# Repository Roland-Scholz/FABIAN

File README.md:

# Fa Bi An
FAbulous BInary ANihilator

A simple Z80 based CP/M system. You'll find here:

- KiCad files for the pcb
- 6-chip Z80 hardware
- 64KB static RAM
- 8/16/32KB (EP)ROM, here a 2764A version is used (8KB, 12,5V pgm voltage)
- 68681 double UART operating at 115200 baud
- one serial line connects to a VT100 terminal, the 2nd one to the CP/M disk server (two TTL to RS232 converters needed)
- GAL 16V8 providing glue logic (fabian.pld, connect PIN 5 and 15 with a pice of wire)
- WinCUPL https://www.microchip.com/en-us/products/fpgas-and-plds/spld-cplds/pld-design-resources)
- CP/M-2.2 and simple BIOS source code (CP/M at $E400, BIOS at $FA00)
- Windows based build files
- Serial CP/M disk server written in Java
- 8 output pins (7 usable, OP7 toggels ROM on/off)
- 6 input pins
- I have some PCBs left, write to rolandscholz@gmx.de if you want one

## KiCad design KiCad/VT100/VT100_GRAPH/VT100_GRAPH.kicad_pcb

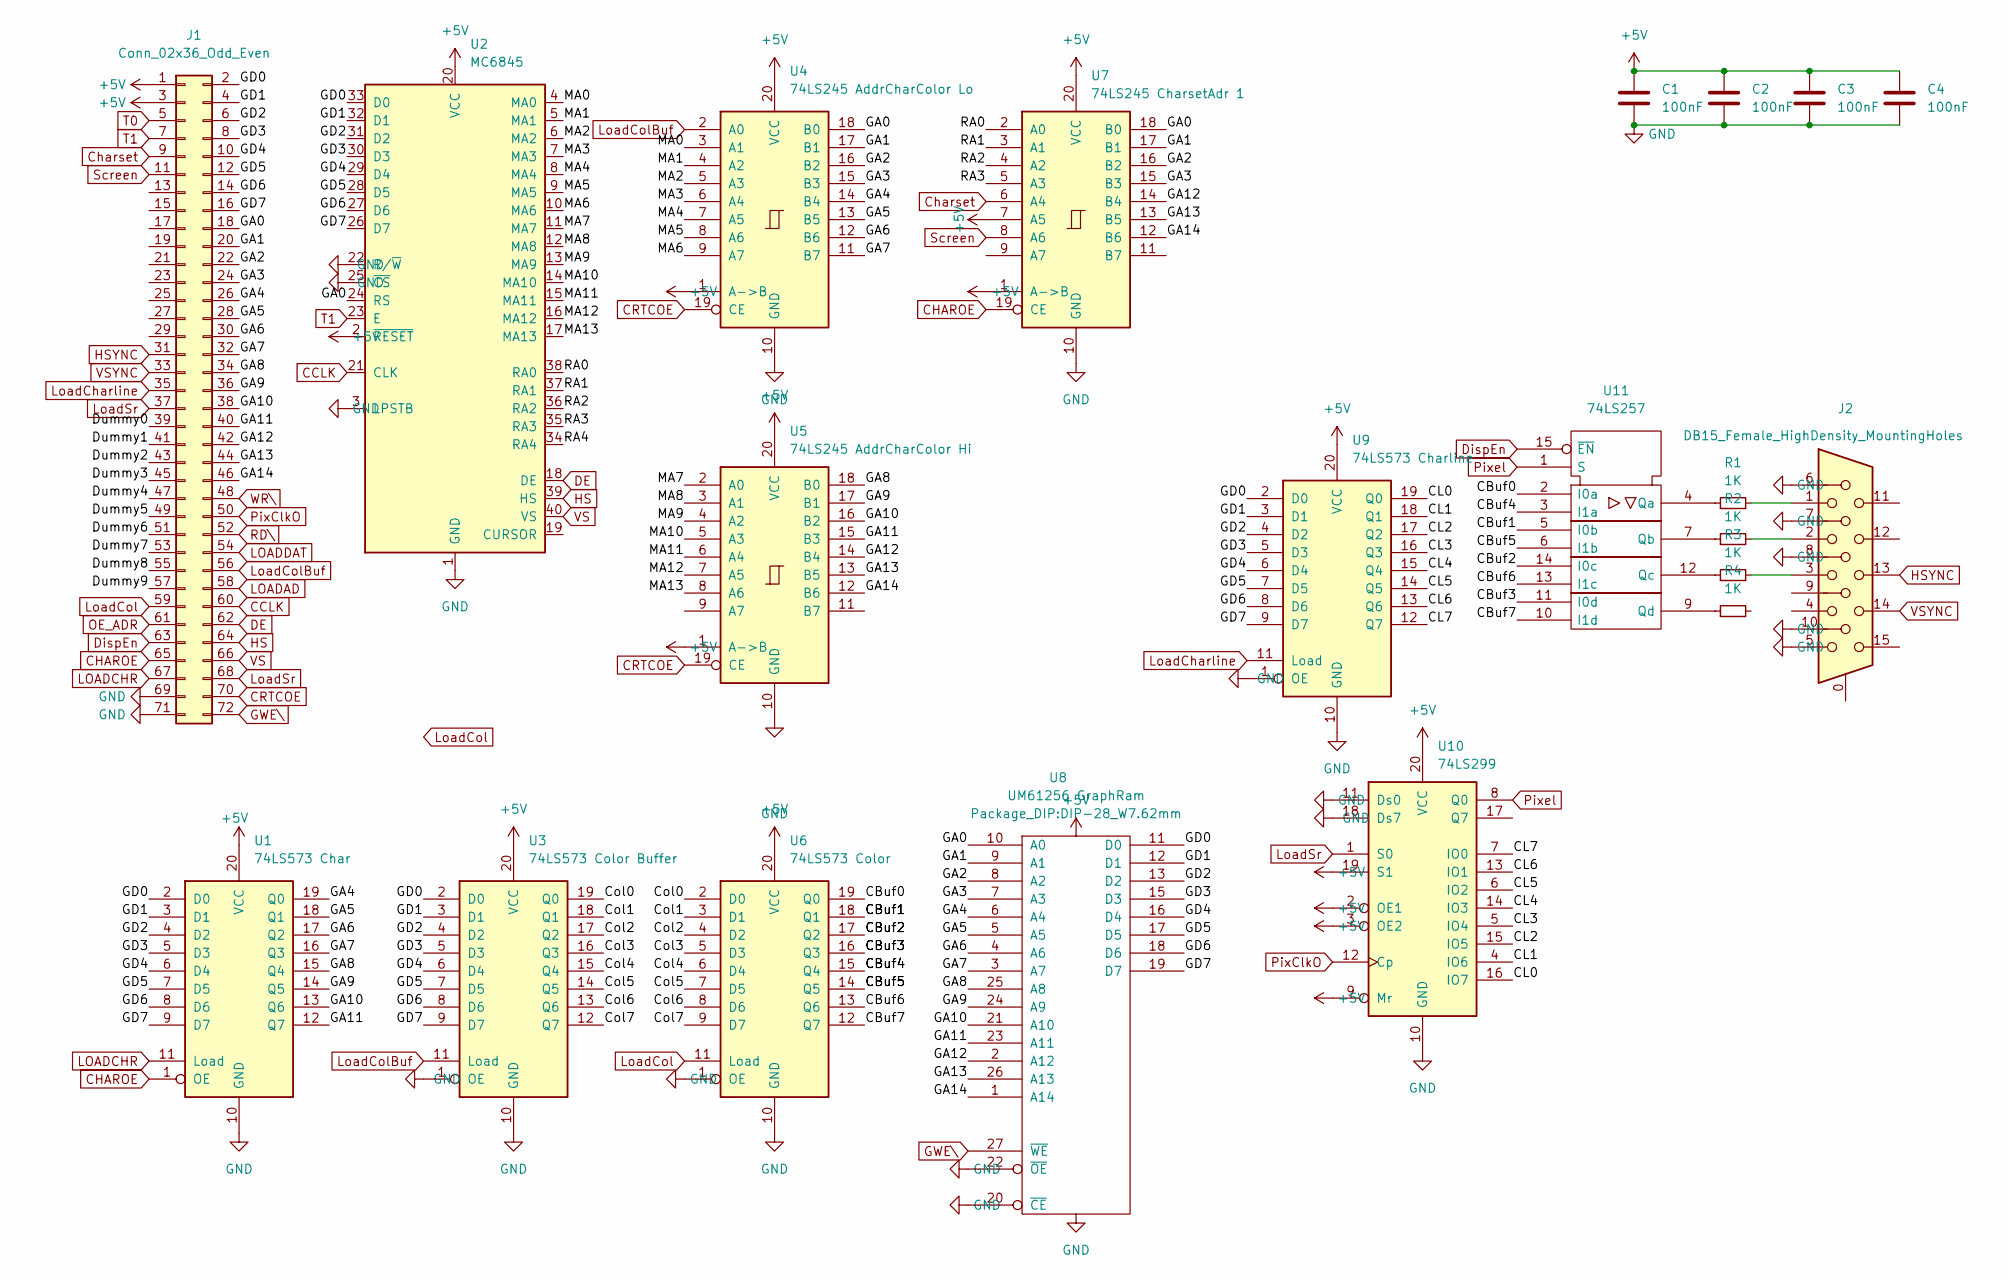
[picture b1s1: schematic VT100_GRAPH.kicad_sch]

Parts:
C1, C2, C3, C4: 100nF; C_Rect_L7.0mm_W2.0mm_P5.00mm
J1: Conn_02x36_Odd_Even; PinSocket_2x36_P2.54mm_Vertical
J2: DB15_Female_HighDensity_MountingHoles; DSUB-15-HD_Female_Horizontal_P2.29x1.98mm_EdgePinOffset3.03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
R1, R2, R3, R4: 1K; R_Axial_DIN0204_L3.6mm_D1.6mm_P1.90mm_Vertical
U1: 74LS573 Char; DIP-20_W7.62mm
U2: MC6845; DIP-40_W15.24mm
U3: 74LS573 Color Buffer; DIP-20_W7.62mm
U4: 74LS245 AddrCharColor Lo; DIP-20_W7.62mm
U5: 74LS245 AddrCharColor Hi; DIP-20_W7.62mm
U6: 74LS573 Color; DIP-20_W7.62mm
U7: 74LS245 CharsetAdr 1; DIP-20_W7.62mm
U8: UM61256 GraphRam; DIP-28_W7.62mm
U9: 74LS573 Charline; DIP-20_W7.62mm
U10: 74LS299; DIP-20_W7.62mm
U11: 74LS257; DIP-16_W7.62mm

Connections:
+5V: C1.1, C2.1, C3.1, C4.1, J1.1, J1.3, U1.20 (VCC), U2.2 (~RESET), U2.20 (VCC), U3.20 (VCC), U4.1 (A->B), U4.20 (VCC), U5.1 (A->B), U5.20 (VCC), U6.20 (VCC), U7.1 (A->B), U7.7 (A5), U7.20 (VCC), U8.28 (VCC), U9.20 (VCC), U10.2 (OE1), U10.3 (OE2), U10.9 (Mr), U10.19 (S1), U10.20 (VCC), U11.16 (VCC)
/CBuf0: U6.19 (Q0), U11.2 (I0a)
/CBuf1: U6.18 (Q1), U11.5 (I0b)
/CBuf2: U6.17 (Q2), U11.14 (I0c)
/CBuf3: U6.16 (Q3), U11.11 (I0d)
/CBuf4: U6.15 (Q4), U11.3 (I1a)
/CBuf5: U6.14 (Q5), U11.6 (I1b)
/CBuf6: U6.13 (Q6), U11.13 (I1c)
/CBuf7: U6.12 (Q7), U11.10 (I1d)
/CL0: U9.19 (Q0), U10.16 (IO7)
/CL1: U9.18 (Q1), U10.4 (IO6)
/CL2: U9.17 (Q2), U10.15 (IO5)
/CL3: U9.16 (Q3), U10.5 (IO4)
/CL4: U9.15 (Q4), U10.14 (IO3)
/CL5: U9.14 (Q5), U10.6 (IO2)
/CL6: U9.13 (Q6), U10.13 (IO1)
/CL7: U9.12 (Q7), U10.7 (IO0)
/Col0: U3.19 (Q0), U6.2 (D0)
/Col1: U3.18 (Q1), U6.3 (D1)
/Col2: U3.17 (Q2), U6.4 (D2)
/Col3: U3.16 (Q3), U6.5 (D3)
/Col4: U3.15 (Q4), U6.6 (D4)
/Col5: U3.14 (Q5), U6.7 (D5)
/Col6: U3.13 (Q6), U6.8 (D6)
/Col7: U3.12 (Q7), U6.9 (D7)
/Dummy0: J1.39
/Dummy1: J1.41
/Dummy2: J1.43
/Dummy3: J1.45
/Dummy4: J1.47
/Dummy5: J1.49
/Dummy6: J1.51
/Dummy7: J1.53
/Dummy8: J1.55
/Dummy9: J1.57
/GA0: J1.18, U2.24 (RS), U4.18 (B0), U7.18 (B0), U8.10 (A0)
/GA1: J1.20, U4.17 (B1), U7.17 (B1), U8.9 (A1)
/GA2: J1.22, U4.16 (B2), U7.16 (B2), U8.8 (A2)
/GA3: J1.24, U4.15 (B3), U7.15 (B3), U8.7 (A3)
/GA4: J1.26, U1.19 (Q0), U4.14 (B4), U8.6 (A4)
/GA5: J1.28, U1.18 (Q1), U4.13 (B5), U8.5 (A5)
/GA6: J1.30, U1.17 (Q2), U4.12 (B6), U8.4 (A6)
/GA7: J1.32, U1.16 (Q3), U4.11 (B7), U8.3 (A7)
/GA8: J1.34, U1.15 (Q4), U5.18 (B0), U8.25 (A8)
/GA9: J1.36, U1.14 (Q5), U5.17 (B1), U8.24 (A9)
/GA10: J1.38, U1.13 (Q6), U5.16 (B2), U8.21 (A10)
/GA11: J1.40, U1.12 (Q7), U5.15 (B3), U8.23 (A11)
/GA12: J1.42, U5.14 (B4), U7.14 (B4), U8.2 (A12)
/GA13: J1.44, U5.13 (B5), U7.13 (B5), U8.26 (A13)
/GA14: J1.46, U5.12 (B6), U7.12 (B6), U8.1 (A14)
/GD0: J1.2, U1.2 (D0), U2.33 (D0), U3.2 (D0), U8.11 (D0), U9.2 (D0)
/GD1: J1.4, U1.3 (D1), U2.32 (D1), U3.3 (D1), U8.12 (D1), U9.3 (D1)
/GD2: J1.6, U1.4 (D2), U2.31 (D2), U3.4 (D2), U8.13 (D2), U9.4 (D2)
/GD3: J1.8, U1.5 (D3), U2.30 (D3), U3.5 (D3), U8.15 (D3), U9.5 (D3)
/GD4: J1.10, U1.6 (D4), U2.29 (D4), U3.6 (D4), U8.16 (D4), U9.6 (D4)
/GD5: J1.12, U1.7 (D5), U2.28 (D5), U3.7 (D5), U8.17 (D5), U9.7 (D5)
/GD6: J1.14, U1.8 (D6), U2.27 (D6), U3.8 (D6), U8.18 (D6), U9.8 (D6)
/GD7: J1.16, U1.9 (D7), U2.26 (D7), U3.9 (D7), U8.19 (D7), U9.9 (D7)
/MA0: U2.4 (MA0), U4.3 (A1)
/MA1: U2.5 (MA1), U4.4 (A2)
/MA2: U2.6 (MA2), U4.5 (A3)
/MA3: U2.7 (MA3), U4.6 (A4)
/MA4: U2.8 (MA4), U4.7 (A5)
/MA5: U2.9 (MA5), U4.8 (A6)
/MA6: U2.10 (MA6), U4.9 (A7)
/MA7: U2.11 (MA7), U5.2 (A0)
/MA8: U2.12 (MA8), U5.3 (A1)
/MA9: U2.13 (MA9), U5.4 (A2)
/MA10: U2.14 (MA10), U5.5 (A3)
/MA11: U2.15 (MA11), U5.6 (A4)
/MA12: U2.16 (MA12), U5.7 (A5)
/MA13: U2.17 (MA13), U5.8 (A6)
/RA0: U2.38 (RA0), U7.2 (A0)
/RA1: U2.37 (RA1), U7.3 (A1)
/RA2: U2.36 (RA2), U7.4 (A2)
/RA3: U2.35 (RA3), U7.5 (A3)
/RA4: U2.34 (RA4)
CCLK: J1.60, U2.21 (CLK)
CHAROE: J1.65, U1.1 (OE), U7.19 (CE)
CRTCOE: J1.70, U4.19 (CE), U5.19 (CE)
Charset: J1.9, U7.6 (A4)
DE: J1.62, U2.18 (DE)
DispEn: J1.63, U11.15 (~EN)
GND: C1.2, C2.2, C3.2, C4.2, J1.69, J1.71, J2.5, J2.6, J2.7, J2.8, J2.10, U1.10 (GND), U2.1 (GND), U2.3 (LPSTB), U2.22 (R/~W), U2.25 (~CS), U3.1 (OE), U3.10 (GND), U4.10 (GND), U5.10 (GND), U6.1 (OE), U6.10 (GND), U7.10 (GND), U8.14 (GND), U8.20 (~CE), U8.22 (~OE), U9.1 (OE), U9.10 (GND), U10.10 (GND), U10.11 (Ds0), U10.18 (Ds7), U11.8 (GND)
GWE\: J1.72, U8.27 (~WE)
HS: J1.64, U2.39 (HS)
HSYNC: J1.31, J2.13
LOADAD: J1.58
LOADCHR: J1.67, U1.11 (Load)
LOADDAT: J1.54
LoadCharline: J1.35, U9.11 (Load)
LoadCol: J1.59, U6.11 (Load)
LoadColBuf: J1.56, U3.11 (Load), U4.2 (A0)
LoadSr: J1.37, J1.68, U10.1 (S0)
unnamed: J2.1, R1.2
unnamed: J2.2, R2.2
unnamed: J2.3, R3.2
unnamed: R1.1, U11.4 (Qa)
unnamed: R2.1, U11.7 (Qb)
unnamed: R3.1, U11.12 (Qc)
unnamed: R4.1, U11.9 (Qd)
OE_ADR: J1.61
PixClkO: J1.50, U10.12 (Cp)
Pixel: U10.8 (Q0), U11.1 (S)
RD\: J1.52
Screen: J1.11, U7.8 (A6)
T0: J1.5
T1: J1.7, U2.23 (E)
VS: J1.66, U2.40 (VS)
VSYNC: J1.33, J2.14
WR\: J1.48

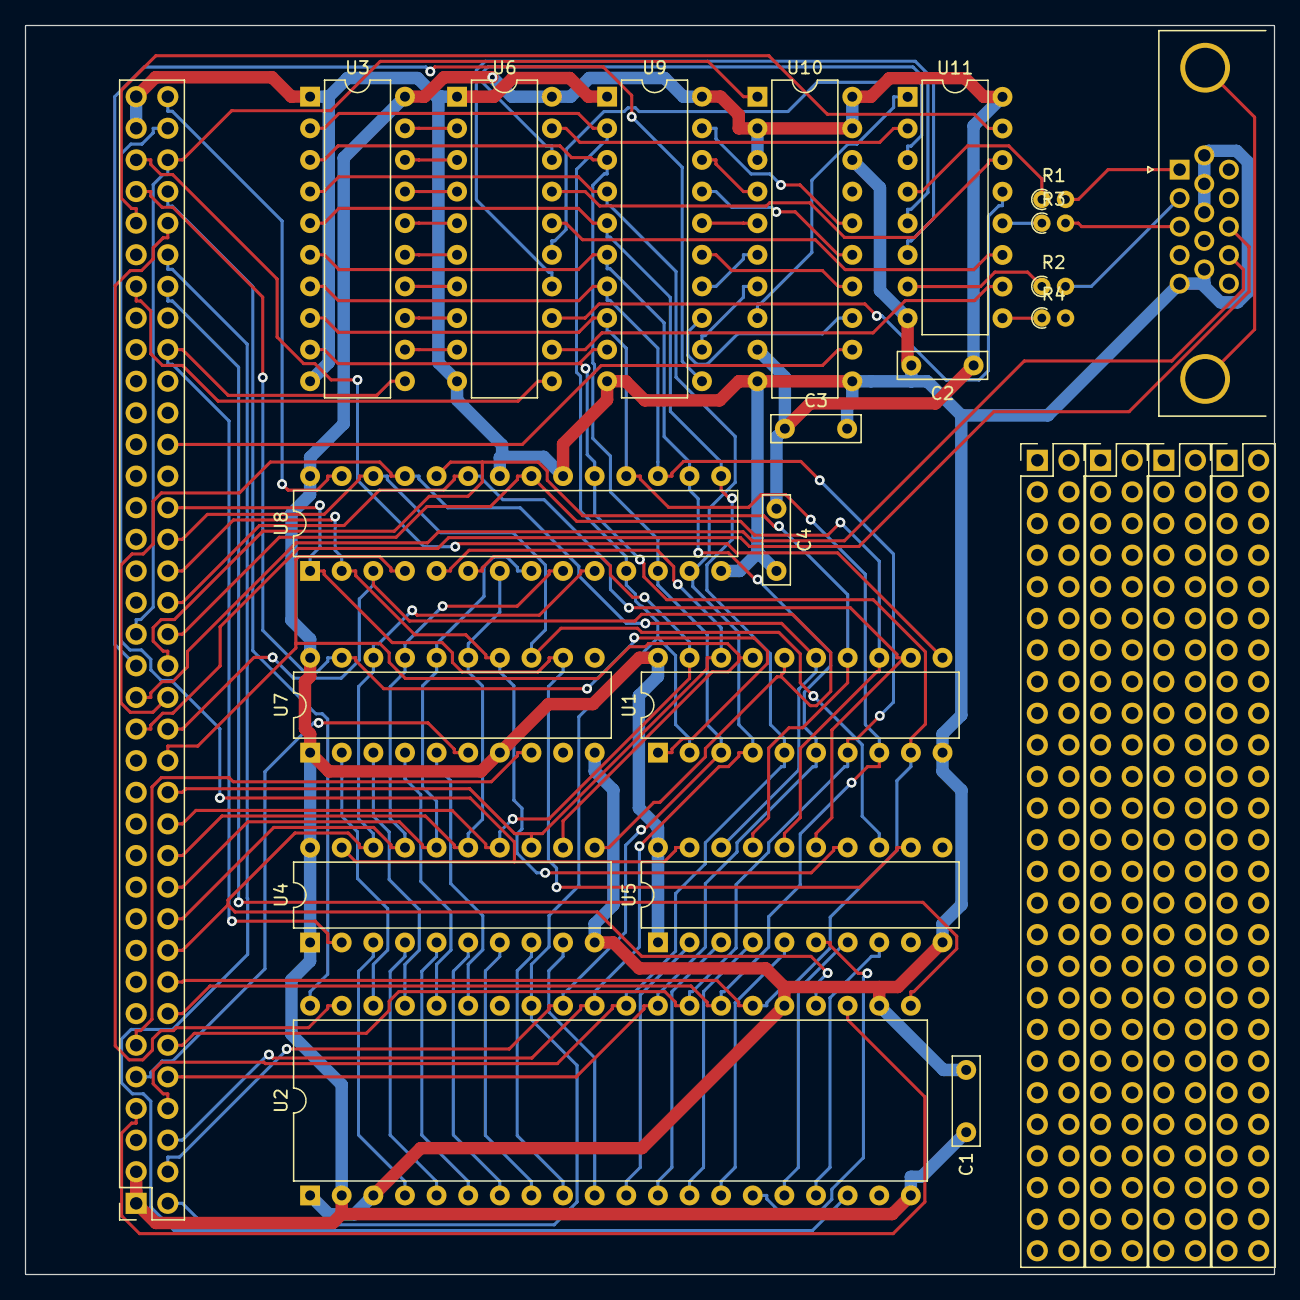
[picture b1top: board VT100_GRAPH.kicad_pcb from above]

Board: 2 copper layers, 100.3 x 100.3 mm, 21 parts (0 on the bottom side), 94 nets.

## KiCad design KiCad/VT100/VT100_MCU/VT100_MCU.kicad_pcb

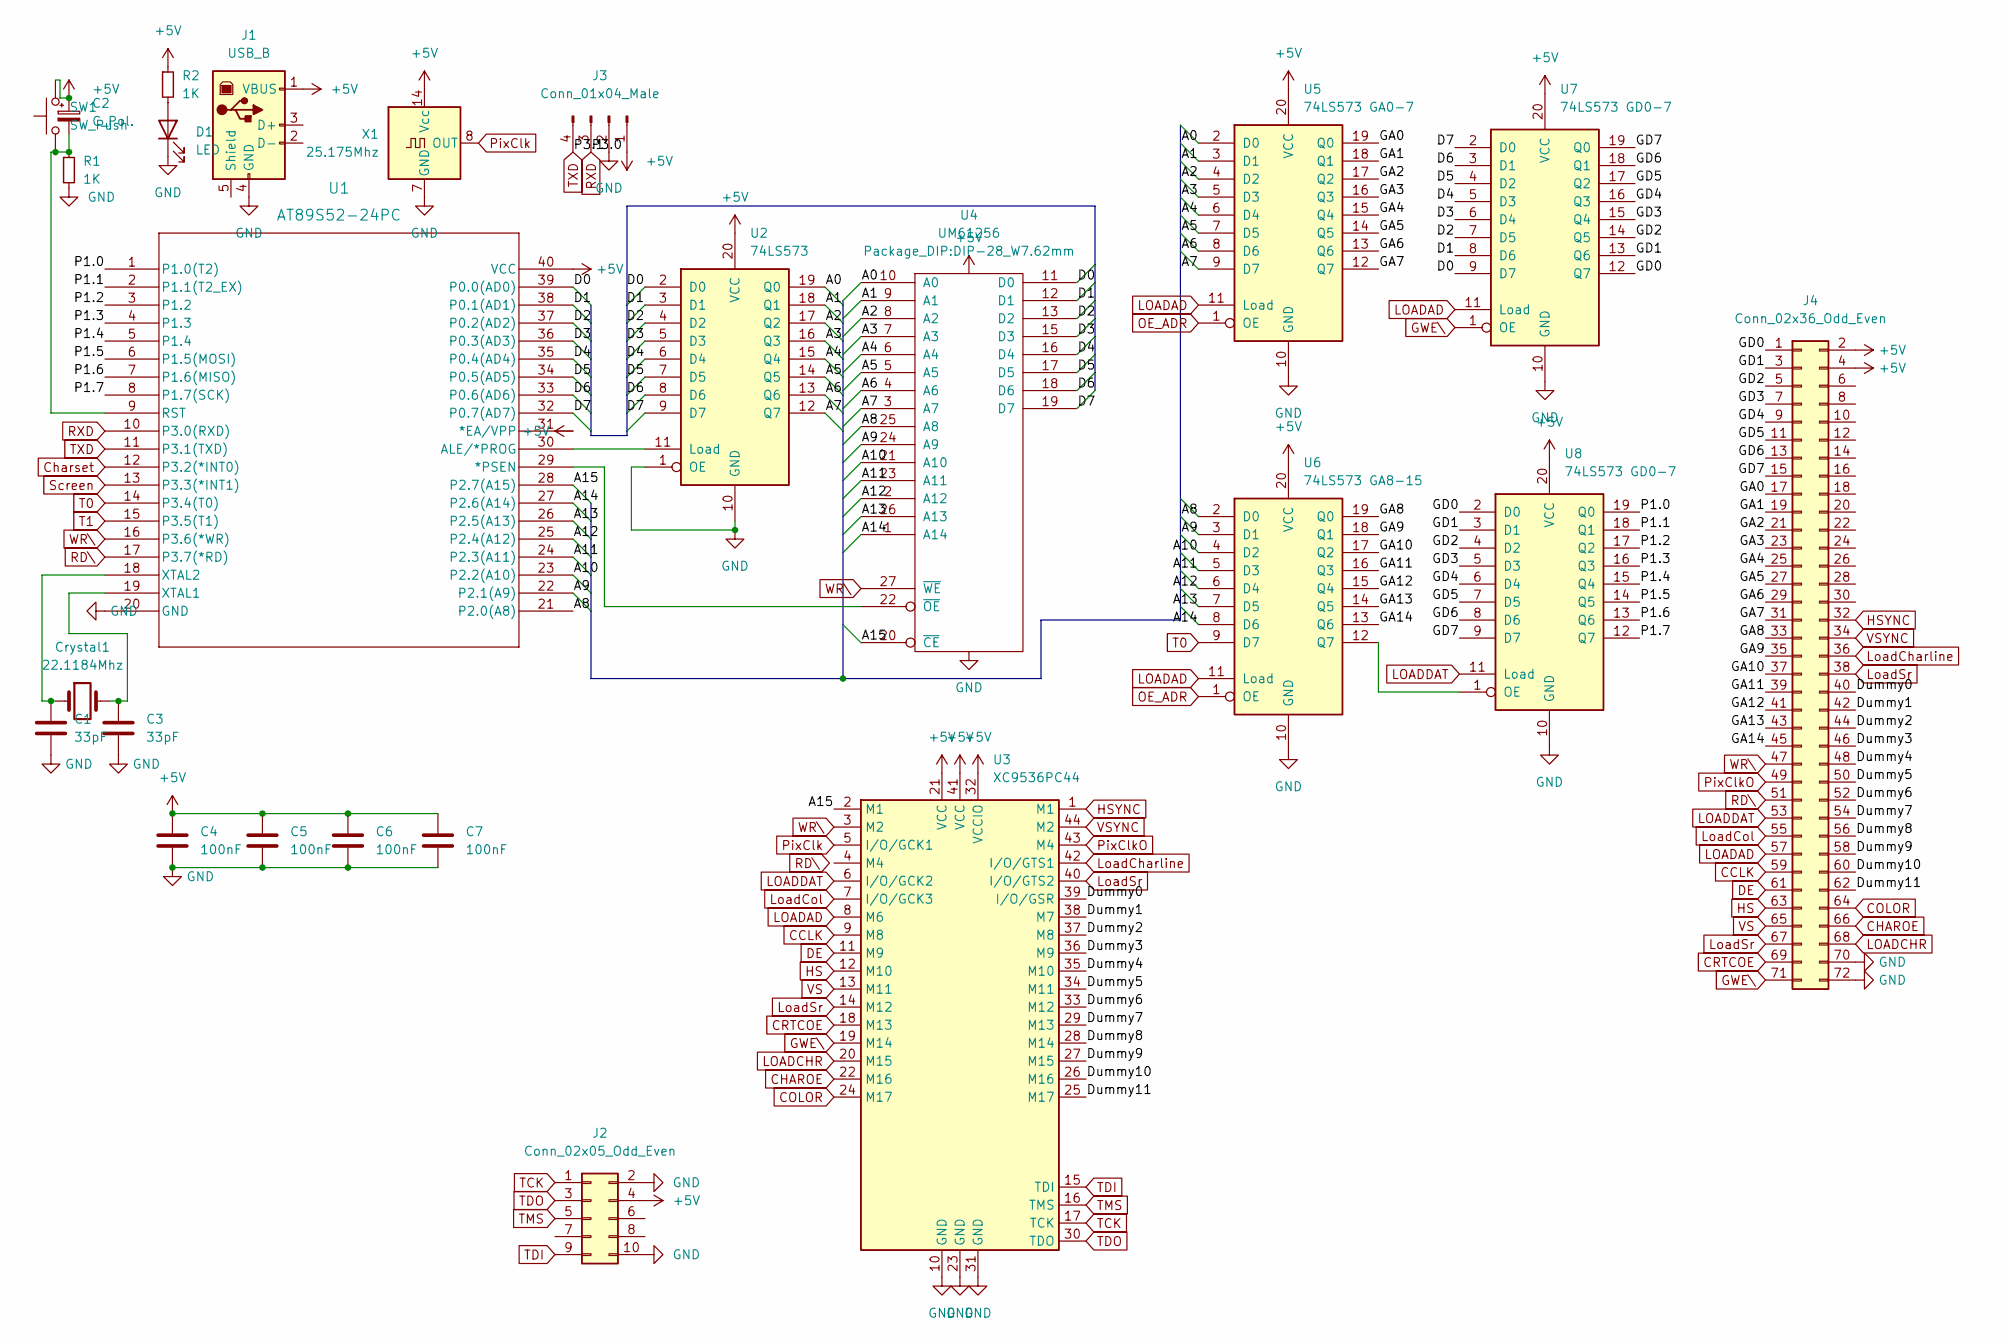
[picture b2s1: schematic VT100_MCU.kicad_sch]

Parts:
C1, C3: 33pF; PinHeader_1x02_P2.54mm_Vertical
C2: C_Pol.; CP_Radial_D5.0mm_P2.50mm
C4, C5, C6, C7: 100nF; PinHeader_1x02_P2.54mm_Vertical
Crystal1: 22.1184Mhz; Crystal_HC18-U_Vertical
D1: LED; LED_D5.0mm
J1: USB_B; USB_B_Lumberg_2411_02_Horizontal
J2: Conn_02x05_Odd_Even; PinHeader_2x05_P2.54mm_Vertical
J3: Conn_01x04_Male; PinHeader_1x04_P2.54mm_Vertical
J4: Conn_02x36_Odd_Even; PinSocket_2x36_P2.54mm_Horizontal
R1, R2: 1K; R_Axial_DIN0204_L3.6mm_D1.6mm_P1.90mm_Vertical
SW1: SW_Push; C_Rect_L7.5mm_W6.5mm_P5.00mm
U1: AT89S52-24PC; DIP-40_W15.24mm
U2: 74LS573; DIP-20_W7.62mm
U3: XC9536PC44; PLCC-44_THT-Socket
U4: UM61256; DIP-28_W7.62mm
U5: 74LS573 GA0-7; DIP-20_W7.62mm
U6: 74LS573 GA8-15; DIP-20_W7.62mm
U7, U8: 74LS573 GD0-7; DIP-20_W7.62mm
X1: 25.175Mhz; Oscillator_DIP-14

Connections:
+5V: C2.1, C4.1, C5.1, C6.1, C7.1, J1.1 (VBUS), J2.4, J3.1, J4.2, J4.4, R2.1, SW1.2, U1.31 (*EA/VPP), U1.40 (VCC), U2.20 (VCC), U3.21 (VCC), U3.32 (VCCIO), U3.41 (VCC), U4.28 (VCC), U5.20 (VCC), U6.20 (VCC), U7.20 (VCC), U8.20 (VCC), X1.14 (Vcc)
/A0: U2.19 (Q0), U4.10 (A0), U5.2 (D0)
/A1: U2.18 (Q1), U4.9 (A1), U5.3 (D1)
/A2: U2.17 (Q2), U4.8 (A2), U5.4 (D2)
/A3: U2.16 (Q3), U4.7 (A3), U5.5 (D3)
/A4: U2.15 (Q4), U4.6 (A4), U5.6 (D4)
/A5: U2.14 (Q5), U4.5 (A5), U5.7 (D5)
/A6: U2.13 (Q6), U4.4 (A6), U5.8 (D6)
/A7: U2.12 (Q7), U4.3 (A7), U5.9 (D7)
/A8: U1.21 (P2.0(A8)), U4.25 (A8), U6.2 (D0)
/A9: U1.22 (P2.1(A9)), U4.24 (A9), U6.3 (D1)
/A10: U1.23 (P2.2(A10)), U4.21 (A10), U6.4 (D2)
/A11: U1.24 (P2.3(A11)), U4.23 (A11), U6.5 (D3)
/A12: U1.25 (P2.4(A12)), U4.2 (A12), U6.6 (D4)
/A13: U1.26 (P2.5(A13)), U4.26 (A13), U6.7 (D5)
/A14: U1.27 (P2.6(A14)), U4.1 (A14), U6.8 (D6)
/A15: U1.28 (P2.7(A15)), U3.2 (M1), U4.20 (~CE)
/D0: U1.39 (P0.0(AD0)), U2.2 (D0), U4.11 (D0), U7.9 (D7)
/D1: U1.38 (P0.1(AD1)), U2.3 (D1), U4.12 (D1), U7.8 (D6)
/D2: U1.37 (P0.2(AD2)), U2.4 (D2), U4.13 (D2), U7.7 (D5)
/D3: U1.36 (P0.3(AD3)), U2.5 (D3), U4.15 (D3), U7.6 (D4)
/D4: U1.35 (P0.4(AD4)), U2.6 (D4), U4.16 (D4), U7.5 (D3)
/D5: U1.34 (P0.5(AD5)), U2.7 (D5), U4.17 (D5), U7.4 (D2)
/D6: U1.33 (P0.6(AD6)), U2.8 (D6), U4.18 (D6), U7.3 (D1)
/D7: U1.32 (P0.7(AD7)), U2.9 (D7), U4.19 (D7), U7.2 (D0)
/Dummy0: J4.40, U3.39 (I/O/GSR)
/Dummy1: J4.42, U3.38 (M7)
/Dummy2: J4.44, U3.37 (M8)
/Dummy3: J4.46, U3.36 (M9)
/Dummy4: J4.48, U3.35 (M10)
/Dummy5: J4.50, U3.34 (M11)
/Dummy6: J4.52, U3.33 (M12)
/Dummy7: J4.54, U3.29 (M13)
/Dummy8: J4.56, U3.28 (M14)
/Dummy9: J4.58, U3.27 (M15)
/Dummy10: J4.60, U3.26 (M16)
/GA0: J4.17, U5.19 (Q0)
/GA1: J4.19, U5.18 (Q1)
/GA2: J4.21, U5.17 (Q2)
/GA3: J4.23, U5.16 (Q3)
/GA4: J4.25, U5.15 (Q4)
/GA5: J4.27, U5.14 (Q5)
/GA6: J4.29, U5.13 (Q6)
/GA7: J4.31, U5.12 (Q7)
/GA8: J4.33, U6.19 (Q0)
/GA9: J4.35, U6.18 (Q1)
/GA10: J4.37, U6.17 (Q2)
/GA11: J4.39, U6.16 (Q3)
/GA12: J4.41, U6.15 (Q4)
/GA13: J4.43, U6.14 (Q5)
/GA14: J4.45, U6.13 (Q6)
/GD0: J4.1, U7.12 (Q7), U8.2 (D0)
/GD1: J4.3, U7.13 (Q6), U8.3 (D1)
/GD2: J4.5, U7.14 (Q5), U8.4 (D2)
/GD3: J4.7, U7.15 (Q4), U8.5 (D3)
/GD4: J4.9, U7.16 (Q3), U8.6 (D4)
/GD5: J4.11, U7.17 (Q2), U8.7 (D5)
/GD6: J4.13, U7.18 (Q1), U8.8 (D6)
/GD7: J4.15, U7.19 (Q0), U8.9 (D7)
/P1.0: U1.1 (P1.0(T2)), U8.19 (Q0)
/P1.1: U1.2 (P1.1(T2_EX)), U8.18 (Q1)
/P1.2: U1.3 (P1.2), U8.17 (Q2)
/P1.3: U1.4 (P1.3), U8.16 (Q3)
/P1.4: U1.5 (P1.4), U8.15 (Q4)
/P1.5: U1.6 (P1.5(MOSI)), U8.14 (Q5)
/P1.6: U1.7 (P1.6(MISO)), U8.13 (Q6)
/P1.7: U1.8 (P1.7(SCK)), U8.12 (Q7)
CCLK: J4.59, U3.9 (M8)
CHAROE: J4.66, U3.22 (M16)
CRTCOE: J4.69, U3.18 (M13)
Charset: J4.10, U1.12 (P3.2(*INT0))
DE: J4.61, U3.11 (M9)
DispEn: J4.64, U3.24 (M17)
GND: C1.2, C3.2, C4.2, C5.2, C6.2, C7.2, D1.1 (K), J1.4 (GND), J2.2, J2.10, J3.2, J4.70, J4.72, R1.2, U1.20 (GND), U2.1 (OE), U2.10 (GND), U3.10 (GND), U3.23 (GND), U3.31 (GND), U4.14 (GND), U5.10 (GND), U6.10 (GND), U7.10 (GND), U8.10 (GND), X1.7 (GND)
GWE\: J4.71, U3.19 (M14), U7.1 (OE)
HS: J4.63, U3.12 (M10)
HSYNC: J4.32, U3.1 (M1)
LOADAD: J4.57, U3.8 (M6), U5.11 (Load), U6.11 (Load), U7.11 (Load)
LOADCHR: J4.68, U3.20 (M15)
LOADDAT: J4.53, U3.6 (I/O/GCK2), U8.11 (Load)
LoadCharline: J4.36, U3.42 (I/O/GTS1)
LoadCol: J4.55, U3.7 (I/O/GCK3)
LoadSr: J4.38, J4.67, U3.14 (M12), U3.40 (I/O/GTS2)
unnamed: C1.1, Crystal1.1, U1.18 (XTAL2)
unnamed: C2.2, R1.1, SW1.1, U1.9 (RST)
unnamed: C3.1, Crystal1.2, U1.19 (XTAL1)
unnamed: D1.2 (A), R2.2
unnamed: U1.29 (*PSEN), U4.22 (~OE)
unnamed: U1.30 (ALE/*PROG), U2.11 (Load)
unnamed: U6.12 (Q7), U8.1 (OE)
PixClk: U3.5 (I/O/GCK1), X1.8 (OUT)
PixClkO: J4.49, U3.43 (M4)
RD\: J4.51, U1.17 (P3.7(*RD)), U3.4 (M4)
RXD: J3.3, U1.10 (P3.0(RXD))
Screen: J4.12, U1.13 (P3.3(*INT1))
T0: J4.6, U1.14 (P3.4(T0)), U6.9 (D7)
T1: J4.8, U1.15 (P3.5(T1))
TCK: J2.1, U3.17 (TCK)
TDI: J2.9, U3.15 (TDI)
TDO: J2.3, U3.30 (TDO)
TMS: J2.5, U3.16 (TMS)
TXD: J3.4, U1.11 (P3.1(TXD))
VS: J4.65, U3.13 (M11)
VSYNC: J4.34, U3.44 (M2)
WR\: J4.47, U1.16 (P3.6(*WR)), U3.3 (M2), U4.27 (~WE)

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
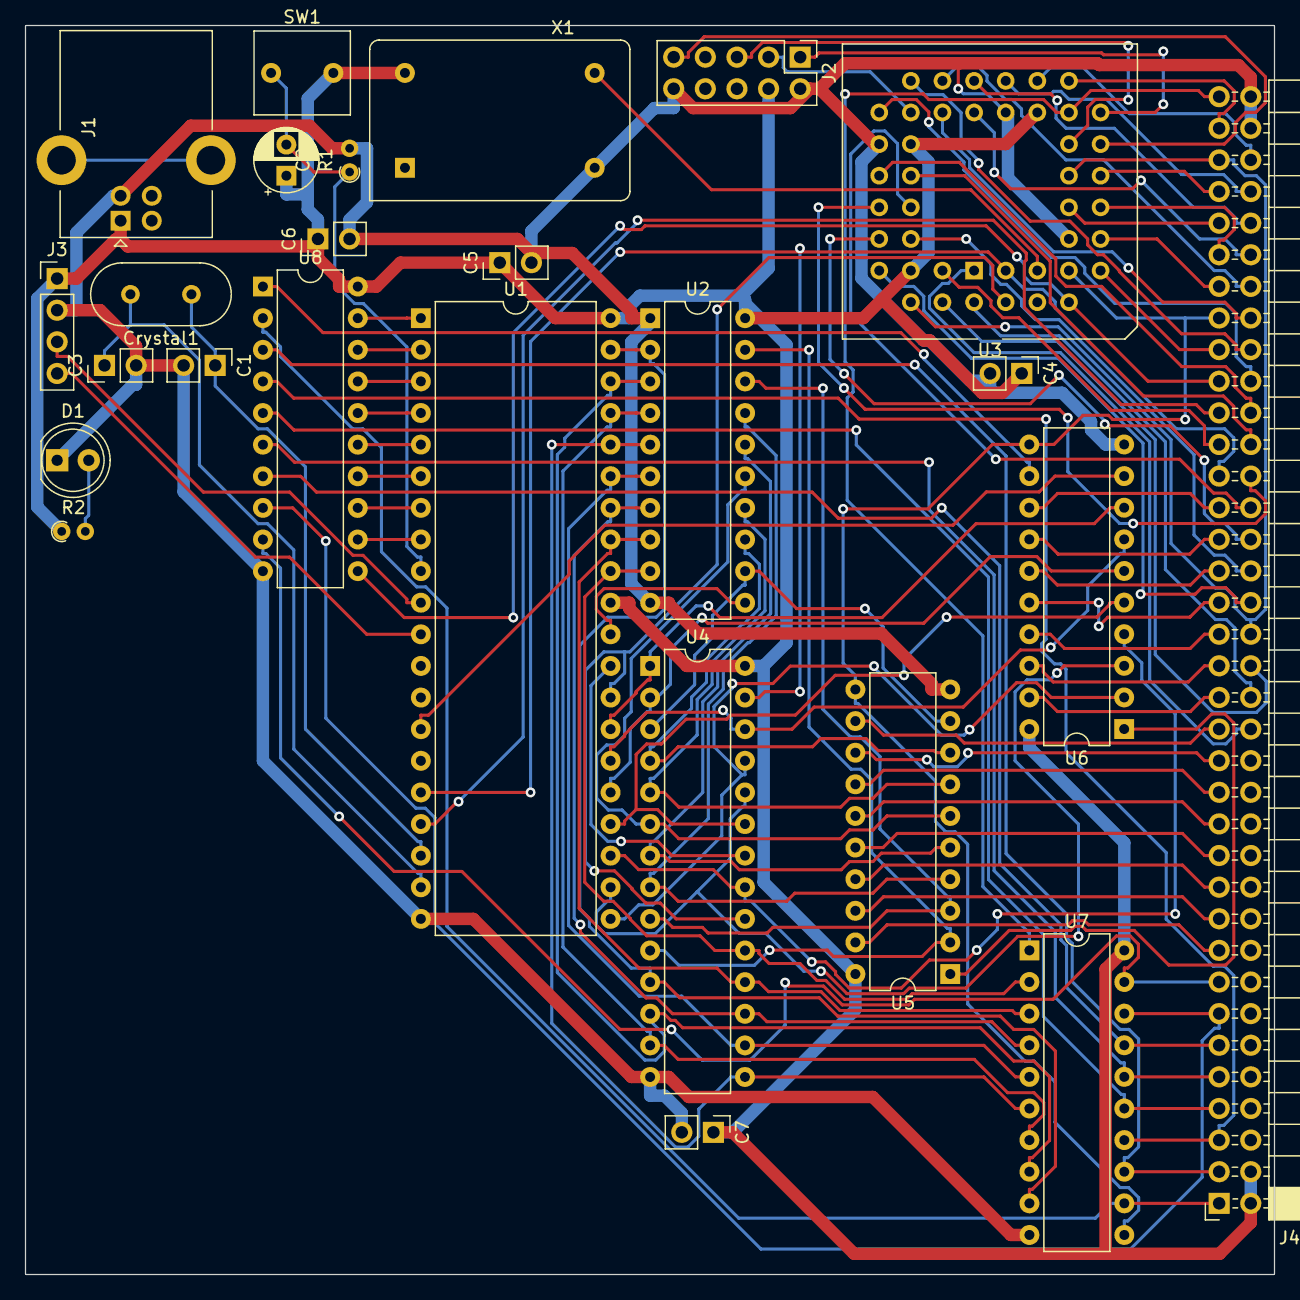
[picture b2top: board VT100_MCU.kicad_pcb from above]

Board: 2 copper layers, 100.3 x 100.3 mm, 25 parts (0 on the bottom side), 106 nets.

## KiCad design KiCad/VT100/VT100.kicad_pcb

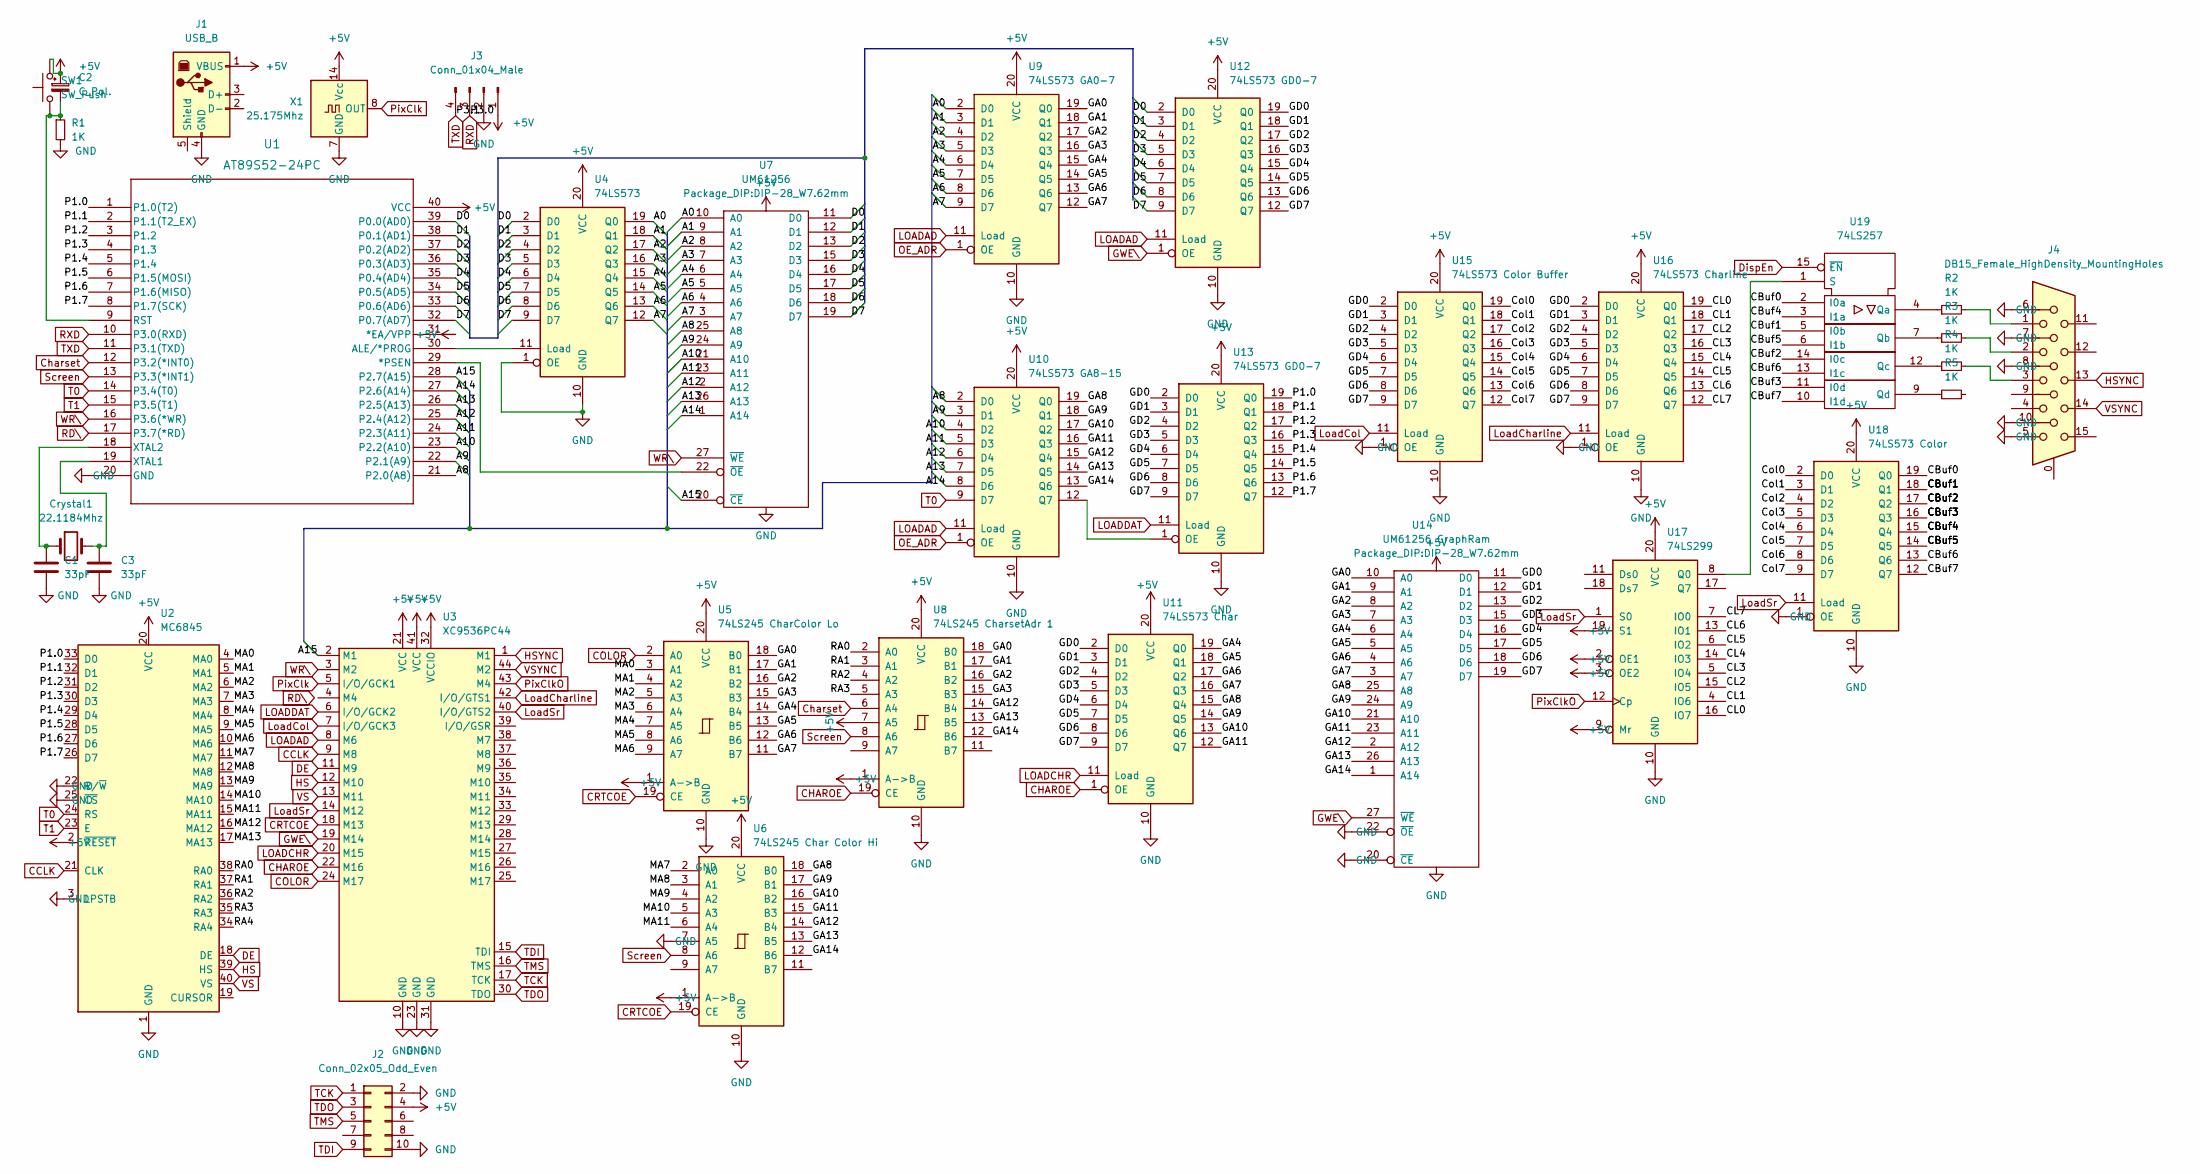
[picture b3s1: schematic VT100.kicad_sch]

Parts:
C1, C3: 33pF; PinHeader_1x02_P2.54mm_Vertical
C2: C_Pol.; CP_Radial_D5.0mm_P2.50mm
Crystal1: 22.1184Mhz; Crystal_HC18-U_Vertical
J1: USB_B; USB_B_Lumberg_2411_02_Horizontal
J2: Conn_02x05_Odd_Even; PinHeader_2x05_P2.54mm_Vertical
J3: Conn_01x04_Male; PinHeader_1x04_P2.54mm_Vertical
J4: DB15_Female_HighDensity_MountingHoles; DSUB-15-HD_Female_Horizontal_P2.29x1.98mm_EdgePinOffset3.03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
R1, R2, R3, R4, R5: 1K; R_Axial_DIN0204_L3.6mm_D1.6mm_P1.90mm_Vertical
SW1: SW_Push; C_Rect_L7.5mm_W6.5mm_P5.00mm
U1: AT89S52-24PC; DIP-40_W15.24mm
U2: MC6845; DIP-40_W15.24mm
U3: XC9536PC44; PLCC-44_THT-Socket
U4: 74LS573; DIP-20_W7.62mm
U5: 74LS245 CharColor Lo; DIP-20_W7.62mm
U6: 74LS245 Char Color Hi; DIP-20_W7.62mm
U7: UM61256; DIP-28_W7.62mm
U8: 74LS245 CharsetAdr 1; DIP-20_W7.62mm
U9: 74LS573 GA0-7; DIP-20_W7.62mm
U10: 74LS573 GA8-15; DIP-20_W7.62mm
U11: 74LS573 Char; DIP-20_W7.62mm
U12, U13: 74LS573 GD0-7; DIP-20_W7.62mm
U14: UM61256 GraphRam; DIP-28_W7.62mm
U15: 74LS573 Color Buffer; DIP-20_W7.62mm
U16: 74LS573 Charline; DIP-20_W7.62mm
U17: 74LS299; DIP-20_W7.62mm
U18: 74LS573 Color; DIP-20_W7.62mm
U19: 74LS257; DIP-16_W7.62mm
X1: 25.175Mhz; Oscillator_DIP-14

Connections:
+5V: C2.1, J1.1 (VBUS), J2.4, J3.1, SW1.2, U1.31 (*EA/VPP), U1.40 (VCC), U2.2 (~RESET), U2.20 (VCC), U3.21 (VCC), U3.32 (VCCIO), U3.41 (VCC), U4.20 (VCC), U5.1 (A->B), U5.20 (VCC), U6.1 (A->B), U6.20 (VCC), U7.28 (VCC), U8.1 (A->B), U8.7 (A5), U8.20 (VCC), U9.20 (VCC), U10.20 (VCC), U11.20 (VCC), U12.20 (VCC), U13.20 (VCC), U14.28 (VCC), U15.20 (VCC), U16.20 (VCC), U17.2 (OE1), U17.3 (OE2), U17.9 (Mr), U17.19 (S1), U17.20 (VCC), U18.20 (VCC), U19.16 (VCC), X1.14 (Vcc)
/A0: U4.19 (Q0), U7.10 (A0), U9.2 (D0)
/A1: U4.18 (Q1), U7.9 (A1), U9.3 (D1)
/A2: U4.17 (Q2), U7.8 (A2), U9.4 (D2)
/A3: U4.16 (Q3), U7.7 (A3), U9.5 (D3)
/A4: U4.15 (Q4), U7.6 (A4), U9.6 (D4)
/A5: U4.14 (Q5), U7.5 (A5), U9.7 (D5)
/A6: U4.13 (Q6), U7.4 (A6), U9.8 (D6)
/A7: U4.12 (Q7), U7.3 (A7), U9.9 (D7)
/A8: U1.21 (P2.0(A8)), U7.25 (A8), U10.2 (D0)
/A9: U1.22 (P2.1(A9)), U7.24 (A9), U10.3 (D1)
/A10: U1.23 (P2.2(A10)), U7.21 (A10), U10.4 (D2)
/A11: U1.24 (P2.3(A11)), U7.23 (A11), U10.5 (D3)
/A12: U1.25 (P2.4(A12)), U7.2 (A12), U10.6 (D4)
/A13: U1.26 (P2.5(A13)), U7.26 (A13), U10.7 (D5)
/A14: U1.27 (P2.6(A14)), U7.1 (A14), U10.8 (D6)
/A15: U1.28 (P2.7(A15)), U3.2 (M1), U7.20 (~CE)
/CBuf0: U18.19 (Q0), U19.2 (I0a)
/CBuf1: U18.18 (Q1), U19.5 (I0b)
/CBuf2: U18.17 (Q2), U19.14 (I0c)
/CBuf3: U18.16 (Q3), U19.11 (I0d)
/CBuf4: U18.15 (Q4), U19.3 (I1a)
/CBuf5: U18.14 (Q5), U19.6 (I1b)
/CBuf6: U18.13 (Q6), U19.13 (I1c)
/CBuf7: U18.12 (Q7), U19.10 (I1d)
/CL0: U16.19 (Q0), U17.16 (IO7)
/CL1: U16.18 (Q1), U17.4 (IO6)
/CL2: U16.17 (Q2), U17.15 (IO5)
/CL3: U16.16 (Q3), U17.5 (IO4)
/CL4: U16.15 (Q4), U17.14 (IO3)
/CL5: U16.14 (Q5), U17.6 (IO2)
/CL6: U16.13 (Q6), U17.13 (IO1)
/CL7: U16.12 (Q7), U17.7 (IO0)
/Col0: U15.19 (Q0), U18.2 (D0)
/Col1: U15.18 (Q1), U18.3 (D1)
/Col2: U15.17 (Q2), U18.4 (D2)
/Col3: U15.16 (Q3), U18.5 (D3)
/Col4: U15.15 (Q4), U18.6 (D4)
/Col5: U15.14 (Q5), U18.7 (D5)
/Col6: U15.13 (Q6), U18.8 (D6)
/Col7: U15.12 (Q7), U18.9 (D7)
/D0: U1.39 (P0.0(AD0)), U4.2 (D0), U7.11 (D0), U12.2 (D0)
/D1: U1.38 (P0.1(AD1)), U4.3 (D1), U7.12 (D1), U12.3 (D1)
/D2: U1.37 (P0.2(AD2)), U4.4 (D2), U7.13 (D2), U12.4 (D2)
/D3: U1.36 (P0.3(AD3)), U4.5 (D3), U7.15 (D3), U12.5 (D3)
/D4: U1.35 (P0.4(AD4)), U4.6 (D4), U7.16 (D4), U12.6 (D4)
/D5: U1.34 (P0.5(AD5)), U4.7 (D5), U7.17 (D5), U12.7 (D5)
/D6: U1.33 (P0.6(AD6)), U4.8 (D6), U7.18 (D6), U12.8 (D6)
/D7: U1.32 (P0.7(AD7)), U4.9 (D7), U7.19 (D7), U12.9 (D7)
/GA0: U5.18 (B0), U8.18 (B0), U9.19 (Q0), U14.10 (A0)
/GA1: U5.17 (B1), U8.17 (B1), U9.18 (Q1), U14.9 (A1)
/GA2: U5.16 (B2), U8.16 (B2), U9.17 (Q2), U14.8 (A2)
/GA3: U5.15 (B3), U8.15 (B3), U9.16 (Q3), U14.7 (A3)
/GA4: U5.14 (B4), U9.15 (Q4), U11.19 (Q0), U14.6 (A4)
/GA5: U5.13 (B5), U9.14 (Q5), U11.18 (Q1), U14.5 (A5)
/GA6: U5.12 (B6), U9.13 (Q6), U11.17 (Q2), U14.4 (A6)
/GA7: U5.11 (B7), U9.12 (Q7), U11.16 (Q3), U14.3 (A7)
/GA8: U6.18 (B0), U10.19 (Q0), U11.15 (Q4), U14.25 (A8)
/GA9: U6.17 (B1), U10.18 (Q1), U11.14 (Q5), U14.24 (A9)
/GA10: U6.16 (B2), U10.17 (Q2), U11.13 (Q6), U14.21 (A10)
/GA11: U6.15 (B3), U10.16 (Q3), U11.12 (Q7), U14.23 (A11)
/GA12: U6.14 (B4), U8.14 (B4), U10.15 (Q4), U14.2 (A12)
/GA13: U6.13 (B5), U8.13 (B5), U10.14 (Q5), U14.26 (A13)
/GA14: U6.12 (B6), U8.12 (B6), U10.13 (Q6), U14.1 (A14)
/GD0: U11.2 (D0), U12.19 (Q0), U13.2 (D0), U14.11 (D0), U15.2 (D0), U16.2 (D0)
/GD1: U11.3 (D1), U12.18 (Q1), U13.3 (D1), U14.12 (D1), U15.3 (D1), U16.3 (D1)
/GD2: U11.4 (D2), U12.17 (Q2), U13.4 (D2), U14.13 (D2), U15.4 (D2), U16.4 (D2)
/GD3: U11.5 (D3), U12.16 (Q3), U13.5 (D3), U14.15 (D3), U15.5 (D3), U16.5 (D3)
/GD4: U11.6 (D4), U12.15 (Q4), U13.6 (D4), U14.16 (D4), U15.6 (D4), U16.6 (D4)
/GD5: U11.7 (D5), U12.14 (Q5), U13.7 (D5), U14.17 (D5), U15.7 (D5), U16.7 (D5)
/GD6: U11.8 (D6), U12.13 (Q6), U13.8 (D6), U14.18 (D6), U15.8 (D6), U16.8 (D6)
/GD7: U11.9 (D7), U12.12 (Q7), U13.9 (D7), U14.19 (D7), U15.9 (D7), U16.9 (D7)
/MA0: U2.4 (MA0), U5.3 (A1)
/MA1: U2.5 (MA1), U5.4 (A2)
/MA2: U2.6 (MA2), U5.5 (A3)
/MA3: U2.7 (MA3), U5.6 (A4)
/MA4: U2.8 (MA4), U5.7 (A5)
/MA5: U2.9 (MA5), U5.8 (A6)
/MA6: U2.10 (MA6), U5.9 (A7)
/MA7: U2.11 (MA7), U6.2 (A0)
/MA8: U2.12 (MA8), U6.3 (A1)
/MA9: U2.13 (MA9), U6.4 (A2)
/MA10: U2.14 (MA10), U6.5 (A3)
/MA11: U2.15 (MA11), U6.6 (A4)
/MA12: U2.16 (MA12)
/MA13: U2.17 (MA13)
/P1.0: U1.1 (P1.0(T2)), U2.33 (D0), U13.19 (Q0)
/P1.1: U1.2 (P1.1(T2_EX)), U2.32 (D1), U13.18 (Q1)
/P1.2: U1.3 (P1.2), U2.31 (D2), U13.17 (Q2)
/P1.3: U1.4 (P1.3), U2.30 (D3), U13.16 (Q3)
/P1.4: U1.5 (P1.4), U2.29 (D4), U13.15 (Q4)
/P1.5: U1.6 (P1.5(MOSI)), U2.28 (D5), U13.14 (Q5)
/P1.6: U1.7 (P1.6(MISO)), U2.27 (D6), U13.13 (Q6)
/P1.7: U1.8 (P1.7(SCK)), U2.26 (D7), U13.12 (Q7)
/RA0: U2.38 (RA0), U8.2 (A0)
/RA1: U2.37 (RA1), U8.3 (A1)
/RA2: U2.36 (RA2), U8.4 (A2)
/RA3: U2.35 (RA3), U8.5 (A3)
/RA4: U2.34 (RA4)
CCLK: U2.21 (CLK), U3.9 (M8)
CHAROE: U3.22 (M16), U8.19 (CE), U11.1 (OE)
COLOR: U3.24 (M17), U5.2 (A0)
CRTCOE: U3.18 (M13), U5.19 (CE), U6.19 (CE)
Charset: U1.12 (P3.2(*INT0)), U8.6 (A4)
DE: U2.18 (DE), U3.11 (M9)
DispEn: U19.15 (~EN)
GND: C1.2, C3.2, J1.4 (GND), J2.2, J2.10, J3.2, J4.5, J4.6, J4.7, J4.8, J4.10, R1.2, U1.20 (GND), U2.1 (GND), U2.3 (LPSTB), U2.22 (R/~W), U2.25 (~CS), U3.10 (GND), U3.23 (GND), U3.31 (GND), U4.1 (OE), U4.10 (GND), U5.10 (GND), U6.7 (A5), U6.10 (GND), U7.14 (GND), U8.10 (GND), U9.10 (GND), U10.10 (GND), U11.10 (GND), U12.10 (GND), U13.10 (GND), U14.14 (GND), U14.20 (~CE), U14.22 (~OE), U15.1 (OE), U15.10 (GND), U16.1 (OE), U16.10 (GND), U17.10 (GND), U18.1 (OE), U18.10 (GND), U19.8 (GND), X1.7 (GND)
GWE\: U3.19 (M14), U12.1 (OE), U14.27 (~WE)
HS: U2.39 (HS), U3.12 (M10)
HSYNC: J4.13, U3.1 (M1)
LOADAD: U3.8 (M6), U9.11 (Load), U10.11 (Load), U12.11 (Load)
LOADCHR: U3.20 (M15), U11.11 (Load)
LOADDAT: U3.6 (I/O/GCK2), U13.11 (Load)
LoadCharline: U3.42 (I/O/GTS1), U16.11 (Load)
LoadCol: U3.7 (I/O/GCK3), U15.11 (Load)
LoadSr: U3.14 (M12), U3.40 (I/O/GTS2), U17.1 (S0), U18.11 (Load)
unnamed: C1.1, Crystal1.1, U1.18 (XTAL2)
unnamed: C2.2, R1.1, SW1.1, U1.9 (RST)
unnamed: C3.1, Crystal1.2, U1.19 (XTAL1)
unnamed: J4.1, R2.2
unnamed: J4.2, R3.2
unnamed: J4.3, R4.2
unnamed: R2.1, U19.4 (Qa)
unnamed: R3.1, U19.7 (Qb)
unnamed: R4.1, U19.12 (Qc)
unnamed: R5.1, U19.9 (Qd)
unnamed: U1.29 (*PSEN), U7.22 (~OE)
unnamed: U1.30 (ALE/*PROG), U4.11 (Load)
unnamed: U10.12 (Q7), U13.1 (OE)
unnamed: U17.8 (Q0), U19.1 (S)
OE_ADR: U9.1 (OE), U10.1 (OE)
PixClk: U3.5 (I/O/GCK1), X1.8 (OUT)
PixClkO: U3.43 (M4), U17.12 (Cp)
RD\: U1.17 (P3.7(*RD))
RXD: J3.3, U1.10 (P3.0(RXD))
Screen: U1.13 (P3.3(*INT1)), U6.8 (A6), U8.8 (A6)
T0: U1.14 (P3.4(T0)), U2.24 (RS), U10.9 (D7)
T1: U1.15 (P3.5(T1)), U2.23 (E)
TCK: J2.1, U3.17 (TCK)
TDI: J2.9, U3.15 (TDI)
TDO: J2.3, U3.30 (TDO)
TMS: J2.5, U3.16 (TMS)
TXD: J3.4, U1.11 (P3.1(TXD))
VS: U2.40 (VS), U3.13 (M11)
VSYNC: J4.14, U3.44 (M2)
WR\: U1.16 (P3.6(*WR)), U3.3 (M2), U7.27 (~WE)

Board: 2 copper layers, 34 parts (0 on the bottom side), 141 nets, no tracks yet.
